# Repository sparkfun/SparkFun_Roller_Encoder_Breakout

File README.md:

SparkFun Roller Encoder Breakout
========================================

[*SparkFun Roller Encoder Breakout (PCB-29094)*](https://www.sparkfun.com/sparkfun-roller-encoder-breakout.html)

A simple breakout board for the EVQWGD001 roller wheel encoder by Panasonic. It is similar to what you might find on a steering wheel or other circa 2000s automotive input. While the EVQWGD001 is not manufactured anymore, it's an often sought after user input because of its feel and unique input mode.

Repository Contents
-------------------

* **[/Firmware](/Firmware)** - An example sketch showing how to read the encoder
* **[/Hardware](/Hardware/)** - Hardware design files

License Information
-------------------

This product is ***open source***!

Please review the [`LICENSE.md`](./LICENSE.md) file for license information.

If you have any questions or concerns about licensing, please contact technical support on our [SparkFun forums](https://community.sparkfun.com/).

Distributed as-is; no warranty is given.

- Your friends at SparkFun.

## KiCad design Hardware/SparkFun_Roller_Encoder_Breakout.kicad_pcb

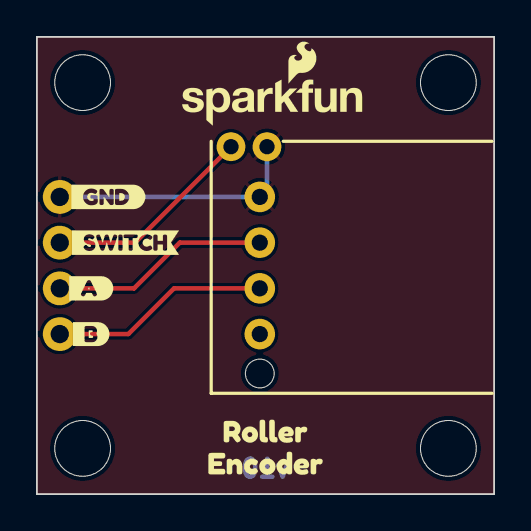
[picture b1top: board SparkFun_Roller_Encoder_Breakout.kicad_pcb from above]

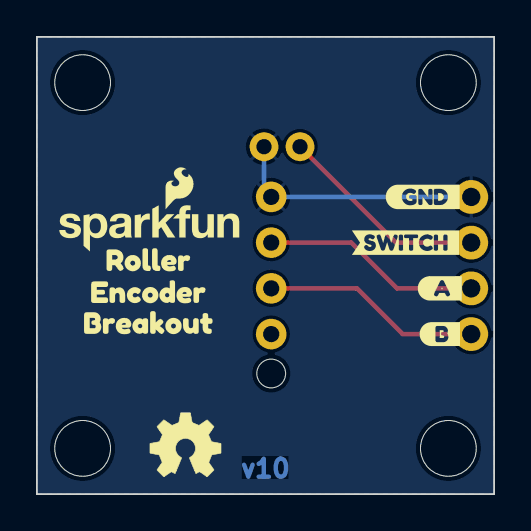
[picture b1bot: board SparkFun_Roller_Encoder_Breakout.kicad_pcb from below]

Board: 2 copper layers, 25.4 x 25.4 mm, 21 parts (8 on the bottom side), 4 nets.

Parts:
G1: OSHW_Logo; Creative_Commons_License
J1: Conn_01x04; 1x04
Ref**: Val**; OSHW_Logo_4mm
ST1, ST2, ST3, ST4: Standoff
SW1: Roller_Encoder_Switch; RollerEncoder
kibuzzard-67946CBF: G***; kibuzzard-67946CBF
kibuzzard-67946CF5: G***; kibuzzard-67946CF5
kibuzzard-67946D1E: G***; kibuzzard-67946D1E
kibuzzard-67946D7C: G***; kibuzzard-67946D7C
kibuzzard-67946D9A: G***; kibuzzard-67946D9A
kibuzzard-67946D71: G***; kibuzzard-67946D71
kibuzzard-67946DB3: G***; kibuzzard-67946DB3
kibuzzard-679465CE, kibuzzard-679465CE#2: G***; kibuzzard-679465CE
kibuzzard-679465D4, kibuzzard-679465D4#2: G***; kibuzzard-679465D4
kibuzzard-6794660B: G***; kibuzzard-6794660B
kibuzzard-6794662B: G***; kibuzzard-6794662B

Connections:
A: J1.2, SW1.A
B: J1.1, SW1.B
GND: J1.4, SW1.C, SW1.S2
SWITCH: J1.3, SW1.S1

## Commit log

2025-04-28 Add readme

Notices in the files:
parts and their libraries:
Released under the Creative Commons Attribution Share-Alike 4.0 License
https://creativecommons.org/licenses/by-sa/4.0
